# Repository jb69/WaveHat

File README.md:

# WaveHat: a sea-state sensor for Signal K, on a Seeed XIAO

A small carrier board ("hat") for a **Seeed XIAO ESP32-C3, C6 or S3** with an ST **LSM6DSO** motion sensor, an **SN65HVD230** CAN transceiver and **256 MB of soldered log storage**. On a yacht it measures how the boat moves and turns that into **heave, significant wave height and wave period** for [Signal K](https://signalk.org), and listens on the NMEA 2000 backbone. The same board runs an eFoil's telemetry node under [VESC Express](https://github.com/vedderb/vesc_express).

## Why

Signal K knows the depth, the wind, the current and even a forecast wave height. It has no **measured** sea state. `environment.heave` is in the specification, and almost nothing fills it; there is no path at all for a measured wave height or period. A boat at anchor is a perfectly good wave buoy if you do the maths on its motion.

## What is here

| Path | What | Licence |
|---|---|---|
| [`hardware/kicad-revB/`](hardware/kicad-revB/) | **Rev B**, the current board (21 × 69 mm): KiCad 10 project, Gerbers, BOM, pick-and-place, JLCPCB and Seeed order packs, and the Python generator that builds all of it from one description | CERN-OHL-S 2.0 |
| [`hardware/kicad/`](hardware/kicad/) | Rev A (21 × 54 mm), the first boards built | CERN-OHL-S 2.0 |
| [`hardware/DESIGN.md`](hardware/DESIGN.md) | Requirements, layout, pin use for C3 / C6 / S3, power, CAN, manufacturing, and what rev A taught (§11) | |
| [`hardware/test-plate/`](hardware/test-plate/) | A printed jig and checklist for testing every via on a bare rev A board | CERN-OHL-S 2.0 |
| [`enclosure/`](enclosure/) | Printable gasketed enclosure: parametric OpenSCAD and STLs | CERN-OHL-S 2.0 |
| [`firmware/`](firmware/) | SensESP firmware (heave, Hs, Tp, Tz to Signal K; NMEA 2000 in, listen-only; on-board CSV log; GNSS port; battery mode), the wave maths in C++ and Python with its test harness and accuracy results, and VESC Express board files | MIT |
| [`signalk-plugin/`](signalk-plugin/) | `signalk-seastate`: a Signal K server plugin that makes a sea state from the heave a Precision-9 compass already puts on NMEA 2000 (PGN 127252). No WaveHat needed | MIT |
| [`docs/signalk-sea-state.md`](docs/signalk-sea-state.md) | The write-up: the gap in Signal K, what the maths does, where the paths land in the spec, and how a boat with a heave-capable compass can try it with no hardware | |
| [`REVIEW.md`](REVIEW.md) | A critical review of the plan and the maths against the objective (21 Oct 2026) | |

## What it sends

| Signal K path | Units | Spec status |
|---|---|---|
| `environment.heave` | m, up positive, 4 Hz | **Standard** |
| `environment.waves.significantHeight` | m, every ~79 s over the last ~20 min | Proposed; mirrors the Weather API's `waveSignificantHeight` |
| `environment.waves.period` | s, peak period Tp; null with no clear peak | Proposed; mirrors `wavePeriod` |
| `environment.waves.meanPeriod` | s, zero-crossing period Tz | Proposed |
| `environment.waves.underway` | bool: the window was taken with the boat moving | Proposed |

How: a Mahony filter finds "up", the acceleration is moved to the hull's roll/pitch centre (you enter where the box is mounted) and rotated to vertical, high-passed at 0.02 Hz and integrated twice to heave; a Welch spectrum over 0.04–0.5 Hz gives Hs = 4 √m0, Tp and Tz. Details and accuracy on synthetic seas (Hs within about 3 % RMS after calibration) are in [`firmware/README.md`](firmware/README.md).

## Status (9 Nov 2026)

Honest version: **no yacht has been to sea with one yet.** The board itself has, in an eFoil.

- **Rev A:** five boards built by JLCPCB in October 2026; brought up on the bench and in service in eFoils under VESC Express. They had open vias from the fab's plating; rev B's layout changes (twinned vias, a test pad per layer crossing) come from that.
- **Rev B:** laid out, checked (ERC 0, DRC 0 errors) and ordered on 7 Nov 2026. Adds a GNSS port (J5), a 10-pin IO header (J6), jumpers that isolate the CAN transceiver (JP8–JP10) and a 1S battery option (J7). Not yet received.
- **Firmware:** builds for all three XIAOs; the wave maths is tested on the desktop and on a bare XIAO C3. The rev B features (GNSS, battery mode with wake-on-motion, bus heave logging) are written and build, and have not run on a board.
- **Signal K plugin:** maths tested against known seas; not yet run against a real compass.

## Limits

- It measures the **boat's** motion, not the water's. A hull filters short chop and can exaggerate swell near its own roll period: expect ±20–30 % on wave height at anchor until it is compared with a buoy.
- **Underway**, waves are met faster or slower than their true period, so periods mean something only at anchor or drifting. The `underway` flag says which.
- One sensor gives no reliable wave **direction**.
- A DIY NMEA 2000 node isn't certified. This one only listens: it never transmits, not even an acknowledge.

## Building one

- **Board:** the order packs in [`hardware/kicad-revB/fab/`](hardware/kicad-revB/fab/) go straight to JLCPCB (`ORDER.md` in each pack has the form settings). Choose electroless copper plating for the vias explicitly.
- **Regenerating the layout:** `hardware/kicad-revB/run_pipeline.sh` needs KiCad 10, Java and [Freerouting](https://github.com/freerouting/freerouting) 2.4.1; point the `FREEROUTING` environment variable at the jar.
- **Firmware:** [PlatformIO](https://platformio.org) with Python 3.10 or newer, then `pio run -e xiao_c3 -t upload` in `firmware/`.
- **Enclosure:** print the base and lid in ASA or PETG and the gasket in TPU; [`enclosure/README.md`](enclosure/README.md).

## Origin

The circuit comes from the telemetry node of a restored Takuma Cruiser V1 eFoil: a XIAO ESP32-C3 with an LSM6DSO and an SN65HVD230 on the ESC's CAN bus, running VESC Express in a sealed box (write-up: foil.zone thread 27157, "Bringing a Dead Takuma Cruiser V1 Back to Life"). WaveHat puts that on one factory-assembled board, keeps its pinout, and adds marine power input, NMEA 2000 and rigid mounting. Some documents here refer to that project's private notes by path; those notes are not in this repository.

## Licences

- Hardware (`hardware/`, `enclosure/`): [CERN-OHL-S 2.0](hardware/LICENSE).
- Software (`firmware/`, `signalk-plugin/`, the generator scripts): [MIT](LICENSE).
- The XIAO footprint in `hardware/kicad*/lib/seeed/` is from Seeed's OPL KiCad library, CC BY-SA 4.0.

## Sources

- ST LSM6DSO: datasheet DS12140, application note AN5192.
- Seeed XIAO pin maps: [ESP32-C3](https://wiki.seeedstudio.com/XIAO_ESP32C3_Getting_Started/), [ESP32-C6](https://wiki.seeedstudio.com/xiao_esp32c6_getting_started/), [ESP32-S3](https://wiki.seeedstudio.com/xiao_esp32s3_getting_started/).
- [VESC Express](https://github.com/vedderb/vesc_express), hardware target `hw_seeed_esp32c3`.
- [Signal K specification](https://github.com/SignalK/specification) and the server's Weather API.
- TI LMR51606 datasheet SLUSEY1B.

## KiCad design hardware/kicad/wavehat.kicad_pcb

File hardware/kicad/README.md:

# WaveHat KiCad project

KiCad 10 schematic and PCB for WaveHat rev A, plus everything needed to order it.

## Files
| File | What |
|---|---|
| `wavehat.kicad_pro`, `wavehat.kicad_sch`, `wavehat.kicad_pcb` | The project. Open `wavehat.kicad_pro` in KiCad |
| `wavehat-schematic.pdf` | Schematic as PDF |
| **`fab/seeed/`** | **Ready for Seeed Fusion**: Gerbers named as Seeed asks, Seeed-format BOMs (with a XIAO C3 / C6 / S3 from Seeed's Open Parts Library, or without), two-sided pick-and-place, assembly drawings, one zip per option, and `ORDER.md` (copied from `ORDER-SEEED.md`) with what to pick on the order forms |
| **`fab/jlcpcb/no-storage/`, `fab/jlcpcb/full/`** | JLCPCB assembly quotes for the top-side-only build and the full two-sided build: JLCPCB-format BOM with LCSC part numbers, CPL (no XIAO), the same Gerbers, and `ORDER.md` (from `ORDER-JLCPCB.md` / `ORDER-JLCPCB-FULL.md`) |
| `fab/wavehat-gerbers.zip` | Gerbers + drill (KiCad names), for PCBWay / JLCPCB |
| `fab/wavehat-bom.csv`, `fab/wavehat-cpl-top.csv`, `fab/wavehat-cpl-bottom.csv` | BOM and pick-and-place for each side (DNP excluded), mm from the board's lower-left corner |
| `img/` | 3D renders, top, bottom and angled |
| `reports/erc.json`, `reports/drc.json` | The last ERC and DRC runs |
| `reports/vias.md` | Every via by net and position, for checking boards with open vias (rev A had some) |
| `lib/wavehat.kicad_sym`, `lib/wavehat.pretty/` | Custom symbols (XIAO 14-pad, LSM6DSO, LMR51606, SD NAND) and footprints (XIAO 14-pad, NMEA 2000 pads, SD NAND LGA-8 8 × 6 mm) |
| `lib/seeed/` | Seeed's original XIAO library files the XIAO footprint is derived from (CC BY-SA 4.0) |
| `wavehat_design.py` | **The source.** Every part, footprint, connection, schematic position and board position |
| `gen_schematic.py`, `gen_pcb.py`, `gen_docs.py`, `gen_seeed.py`, `run_pipeline.sh` | Generators and the end-to-end script |
| `ORDER-SEEED.md` | Seeed Fusion order notes (source of `fab/seeed/ORDER.md`) |

## How it's built
Everything comes from `wavehat_design.py`:
1. `gen_schematic.py` writes the schematic. Every pin gets a short wire and a net label, so the drawing is a connectivity schematic rather than a hand-drawn one. It is checked with `kicad-cli sch erc`.
2. `gen_pcb.py place` builds the board in KiCad's own Python: outline, footprints linked to the schematic symbols by UUID (top, or bottom for the log storage), nets, keep-outs (nothing under the IMU; no vias near the XIAO's underside pads or the fiducials), silkscreen, the drill/place origin at the lower-left corner, and the design rules in the project file. It exports a Specctra DSN with the clearance raised to 0.17 mm for the router.
3. **Freerouting** routes every net, ground included.
4. `gen_pcb.py import` brings the routes back, widens the few pad-entry segments Freerouting thins below 0.15 mm (the 0.02 mm routing margin keeps their clearance), adds ground stitching vias where they clear everything, pours ground on both layers, fills, and removes any stitching via the pour left in an island.
5. `kicad-cli pcb drc --schematic-parity` checks it. If DRC finds an error or anything unconnected, steps 2–5 repeat from a freshly placed board with a different number of Freerouting passes (100, 150, 200, 80, 250, 120), up to six times. The script then exports Gerbers, drill, BOM, both CPLs, the PDF and renders; `gen_docs.py` regenerates `../netlist.md` and `../bom.csv`, and `gen_seeed.py` builds `fab/seeed/`.

To change the design, edit `wavehat_design.py` and run:

```bash
FREEROUTING=/path/to/freerouting-2.4.1.jar ./run_pipeline.sh
```

Hand edits in KiCad are fine too, but they are overwritten the next time the pipeline runs. Once you start polishing the layout by hand, stop regenerating the PCB, and keep `wavehat_design.py` for the schematic and docs only.

## Rules
| | |
|---|---|
| Signal track / clearance | 0.15 mm / 0.15 mm (6 mil, base capability at PCBWay, JLCPCB, Seeed Fusion) |
| Power track (VIN_RAW, VIN_FUSED, VIN, SW, 5V_BUCK, 5V_CAN, XIAO_5V) | 0.4 mm |
| Vias | 0.6 mm pad / 0.3 mm drill, tented |
| Copper to edge | 0.3 mm |

## Last check (20 Oct 2026: log storage, 5–30 V input)
ERC 0 violations · DRC 0 errors, 0 unconnected · schematic parity 0 issues · 59 silkscreen warnings (cosmetic).

## Tools used
- KiCad 10.0.7 (Homebrew cask `kicad`), using `kicad-cli` and the bundled Python `pcbnew` module.
- Freerouting 2.4.1 (https://github.com/freerouting/freerouting/releases/tag/v2.4.1), SHA-256 `251101c3eeac22d7e7dfcf6796603279e5d1000283eb82d8f093780f7afc6aa9`, checked against GitHub's published asset digest. The newest release (2.5.0) was skipped as less than two weeks old.
- OpenJDK (Homebrew `openjdk`) to run Freerouting.

## Sources and licences
- XIAO footprint: derived from Seeed-Studio/OPL_Kicad_Library `XIAO-ESP32-C3-SMD` (pads 15 and up removed so it fits the C3, C6 and S3). That library is **CC BY-SA 4.0**, so `lib/wavehat.pretty/XIAO_ESP32_14P_SMD.kicad_mod` is too. Pad map checked against Seeed's C3, C6 and S3 SMD footprints and symbols.
- LSM6DSO pin functions: ST application note AN5192. LMR51606 pins and the 5 V component values: TI datasheet SLUSEY1B.
- SD NAND pinout (SPI mode) and LGA-8 package: Zetta ZDSD01G/02G/04G datasheet (LCSC C2875853), MK MKDV4GCL (C7500178), CS-Creative CSNP4GCR01 and XTX XTSD04G datasheets; all share the pinout and 8 × 6 mm package.
- Other symbols and footprints: the KiCad standard libraries (CC BY-SA 4.0 with KiCad's exception for designs that use them).
- Circuit origin: the Takuma project's XIAO node (see `../DESIGN.md` §0).

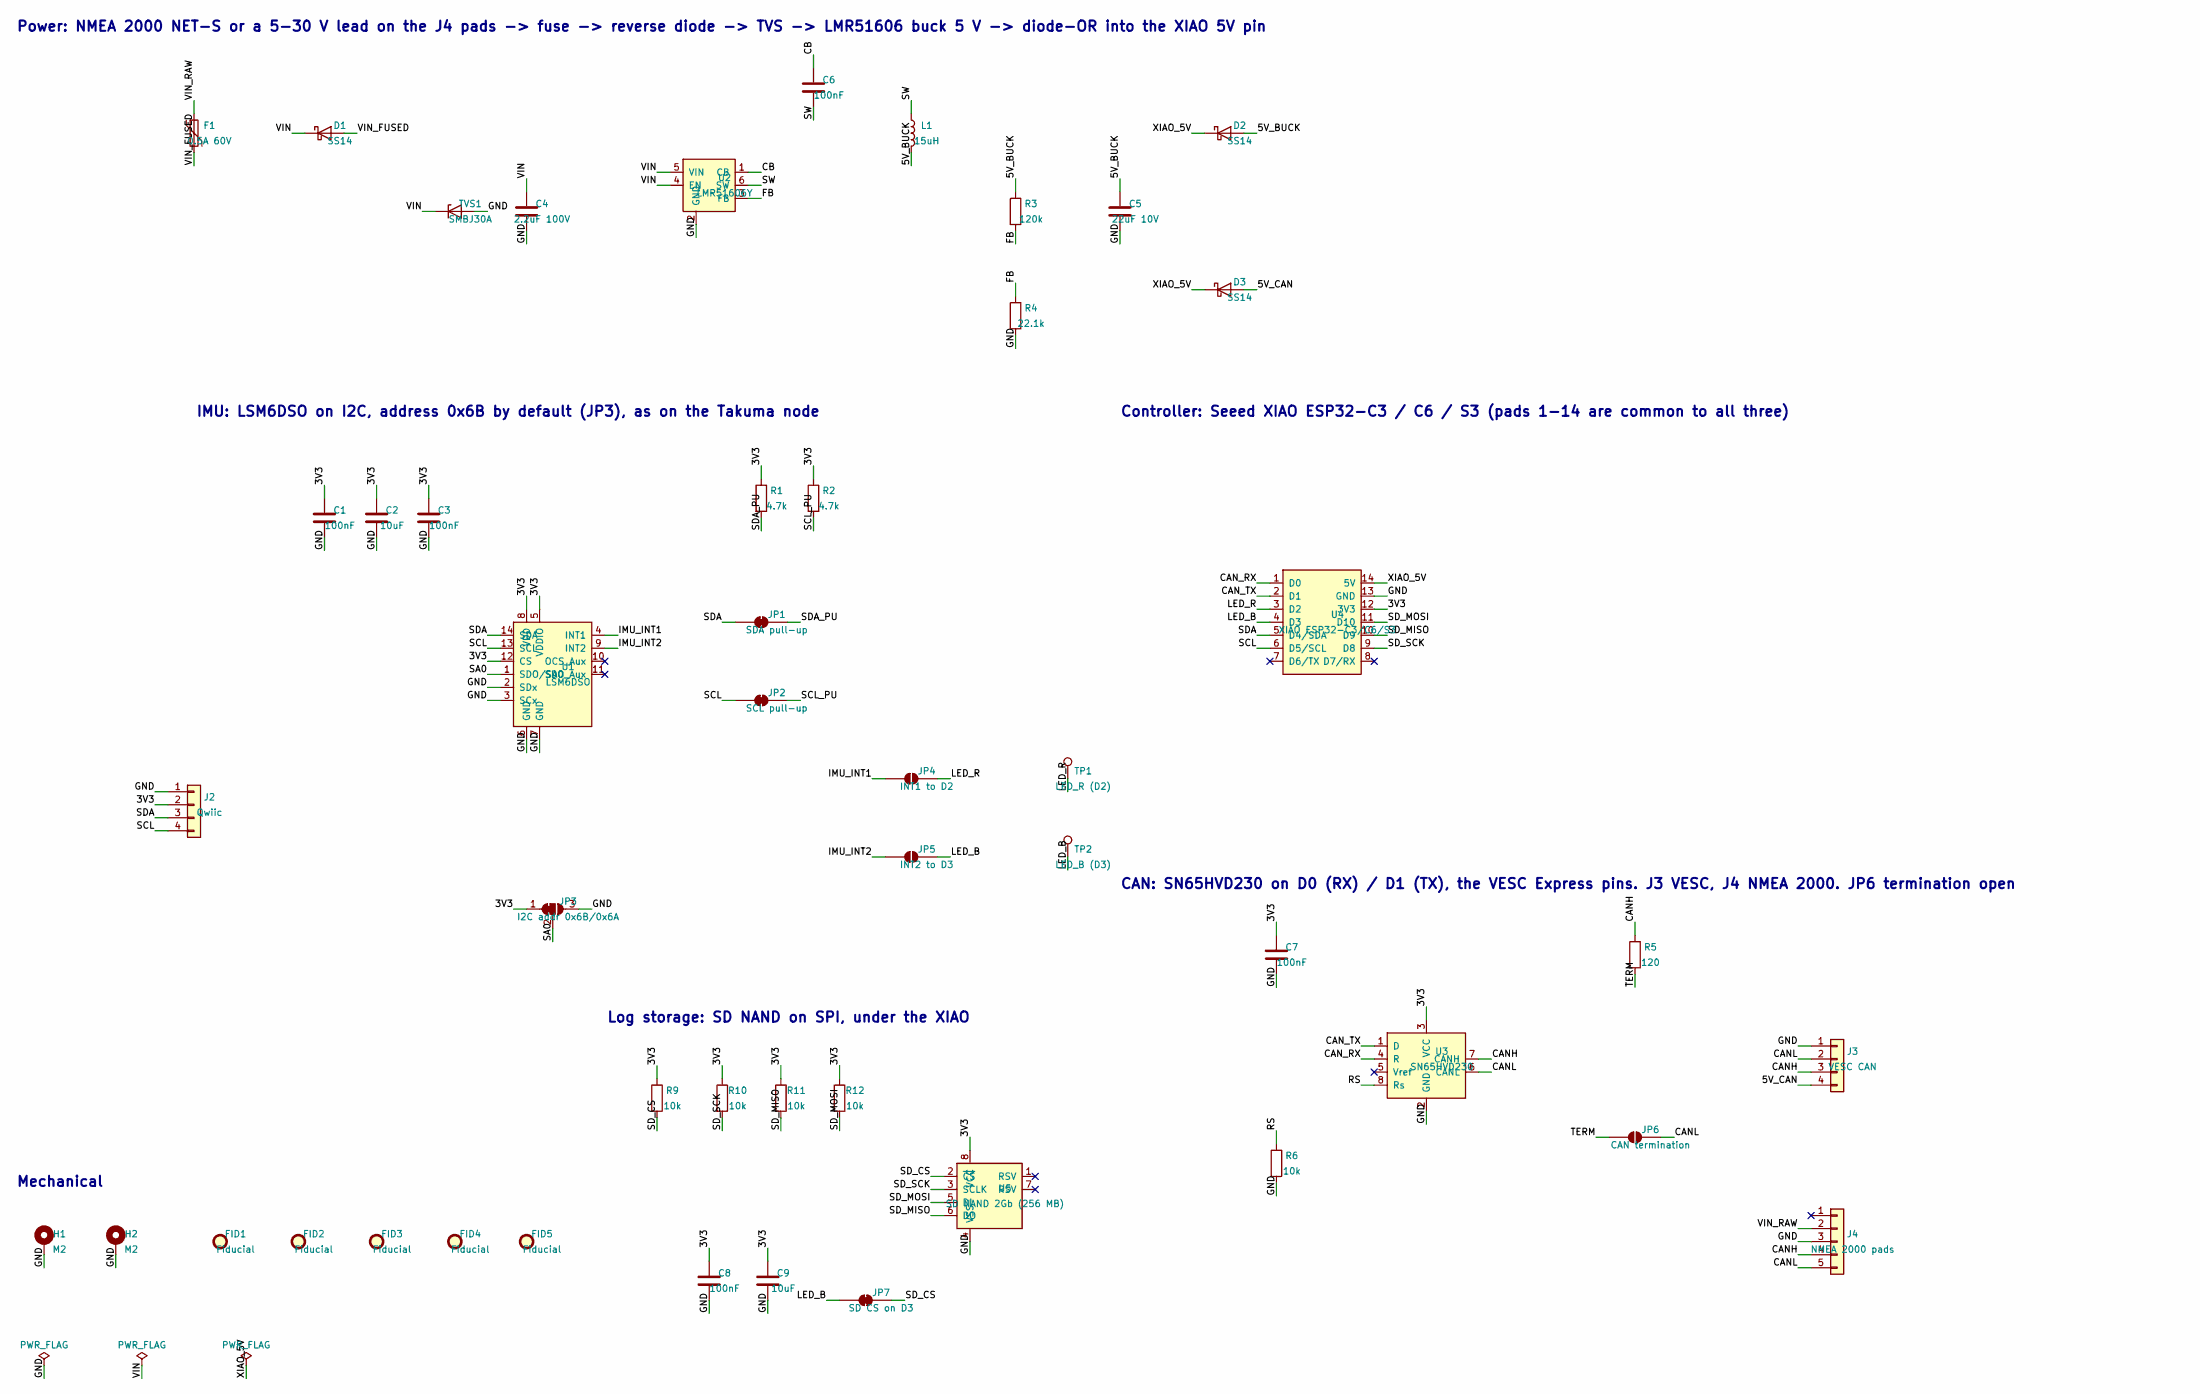
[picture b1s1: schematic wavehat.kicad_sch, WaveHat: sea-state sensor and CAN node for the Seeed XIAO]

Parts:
C1, C3, C6, C7, C8: 100nF; C_0402_1005Metric; MPN GRM155R71C104KA88D
C2, C9: 10uF; C_0603_1608Metric; MPN GRM188R61A106KE69D
C4: 2.2uF 100V; C_1206_3216Metric; MPN GRM31CR72A225KA73L
C5: 22uF 10V; C_0805_2012Metric; MPN GRM21BR61A226ME51L
D1, D2, D3: SS14; D_SMA; MPN SS14
F1: 0.5A 60V; Fuse_1812_4532Metric; MPN 1812L050/60MR
FID1, FID2, FID3, FID4, FID5: Fiducial; Fiducial_1mm_Mask2mm
H1, H2: M2; MountingHole_2.2mm_M2_Pad
J2: Qwiic; JST_SH_SM04B-SRSS-TB_1x04-1MP_P1.00mm_Horizontal; MPN SM04B-SRSS-TB(LF)(SN)
J3: VESC CAN; JST_GH_SM04B-GHS-TB_1x04-1MP_P1.25mm_Horizontal; MPN SM04B-GHS-TB(LF)(SN)
J4: NMEA 2000 pads; N2K_Pads_1x05_P3.0mm
JP1: SDA pull-up; SolderJumper-2_P1.3mm_Bridged_RoundedPad1.0x1.5mm
JP2: SCL pull-up; SolderJumper-2_P1.3mm_Bridged_RoundedPad1.0x1.5mm
JP3: I2C addr 0x6B/0x6A; SolderJumper-3_P1.3mm_Bridged12_RoundedPad1.0x1.5mm
JP4: INT1 to D2; SolderJumper-2_P1.3mm_Open_RoundedPad1.0x1.5mm
JP5: INT2 to D3; SolderJumper-2_P1.3mm_Open_RoundedPad1.0x1.5mm
JP6: CAN termination; SolderJumper-2_P1.3mm_Open_RoundedPad1.0x1.5mm
JP7: SD CS on D3; SolderJumper-2_P1.3mm_Bridged_RoundedPad1.0x1.5mm
L1: 15uH; L_Changjiang_FNR4020S; MPN FNR4020S150MT
R1, R2: 4.7k; R_0402_1005Metric; MPN RC0402FR-074K7L
R3: 120k; R_0402_1005Metric; MPN RC0402FR-07120KL
R4: 22.1k; R_0402_1005Metric; MPN RC0402FR-0722K1L
R5: 120; R_0402_1005Metric; MPN RC0402FR-07120RL
R6, R9, R10, R11, R12: 10k; R_0402_1005Metric; MPN RC0402FR-0710KL
TP1: LED_R (D2); TestPoint_Pad_D1.5mm
TP2: LED_B (D3); TestPoint_Pad_D1.5mm
TVS1: SMBJ30A; D_SMB; MPN SMBJ30A
U1: LSM6DSO; LGA-14_3x2.5mm_P0.5mm_LayoutBorder3x4y; MPN LSM6DSOTR
U2: LMR51606Y; SOT-23-6; MPN LMR51606YDBVR
U3: SN65HVD230; SOIC-8_3.9x4.9mm_P1.27mm; MPN SN65HVD230DR
U4: XIAO ESP32-C3/C6/S3; XIAO_ESP32_14P_SMD; MPN Seeed XIAO ESP32C3 113991054 (or C6 113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
U5: SD NAND 2Gb (256 MB); SD_NAND_LGA-8_8x6mm_P1.27mm; MPN ZDSD02GLGEAG

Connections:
/3V3: C1.1, C2.1, C3.1, C7.1, C8.1, C9.1, J2.2, JP3.1 (A), R1.1, R2.1, R9.1, R10.1, R11.1, R12.1, U1.5 (VDDIO), U1.8 (VDD), U1.12 (CS), U3.3 (VCC), U4.12 (3V3), U5.8 (VCC)
/5V_BUCK: C5.1, D2.2 (A), L1.2, R3.1
/5V_CAN: D3.2 (A), J3.4
/CANH: J3.3, J4.4, R5.1, U3.7 (CANH)
/CANL: J3.2, J4.5, JP6.2 (B), U3.6 (CANL)
/CAN_RX: U3.4 (R), U4.1 (D0)
/CAN_TX: U3.1 (D), U4.2 (D1)
/CB: C6.1, U2.1 (CB)
/FB: R3.2, R4.1, U2.3 (FB)
/GND: C1.2, C2.2, C3.2, C4.2, C5.2, C7.2, C8.2, C9.2, H1.1, H2.1, J2.1, J3.1, J4.3, JP3.3 (B), R4.2, R6.2, TVS1.2 (A), U1.2 (SDx), U1.3 (SCx), U1.6 (GND), U1.7 (GND), U2.2 (GND), U3.2 (GND), U4.13 (GND), U5.4 (VSS)
/IMU_INT1: JP4.1 (A), U1.4 (INT1)
/IMU_INT2: JP5.1 (A), U1.9 (INT2)
/LED_B: JP5.2 (B), JP7.1 (A), TP2.1, U4.4 (D3)
/LED_R: JP4.2 (B), TP1.1, U4.3 (D2)
/RS: R6.1, U3.8 (Rs)
/SA0: JP3.2 (C), U1.1 (SDO/SA0)
/SCL: J2.4, JP2.1 (A), U1.13 (SCL), U4.6 (D5/SCL)
/SCL_PU: JP2.2 (B), R2.2
/SDA: J2.3, JP1.1 (A), U1.14 (SDA), U4.5 (D4/SDA)
/SDA_PU: JP1.2 (B), R1.2
/SD_CS: JP7.2 (B), R9.2, U5.2 (~CS)
/SD_MISO: R11.2, U4.10 (D9), U5.6 (DO)
/SD_MOSI: R12.2, U4.11 (D10), U5.5 (DI)
/SD_SCK: R10.2, U4.9 (D8), U5.3 (SCLK)
/SW: C6.2, L1.1, U2.6 (SW)
/TERM: JP6.1 (A), R5.2
/VIN: C4.1, D1.1 (K), TVS1.1 (K), U2.4 (EN), U2.5 (VIN)
/VIN_FUSED: D1.2 (A), F1.2
/VIN_RAW: F1.1, J4.2
/XIAO_5V: D2.1 (K), D3.1 (K), U4.14 (5V)

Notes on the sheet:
Power: NMEA 2000 NET-S or a 5-30 V lead on the J4 pads -> fuse -> reverse diode -> TVS -> LMR51606 buck 5 V -> diode-OR into the XIAO 5V pin
IMU: LSM6DSO on I2C, address 0x6B by default (JP3), as on the Takuma node
Controller: Seeed XIAO ESP32-C3 / C6 / S3 (pads 1-14 are common to all three)
CAN: SN65HVD230 on D0 (RX) / D1 (TX), the VESC Express pins. J3 VESC, J4 NMEA 2000. JP6 termination open
Log storage: SD NAND on SPI, under the XIAO
Mechanical

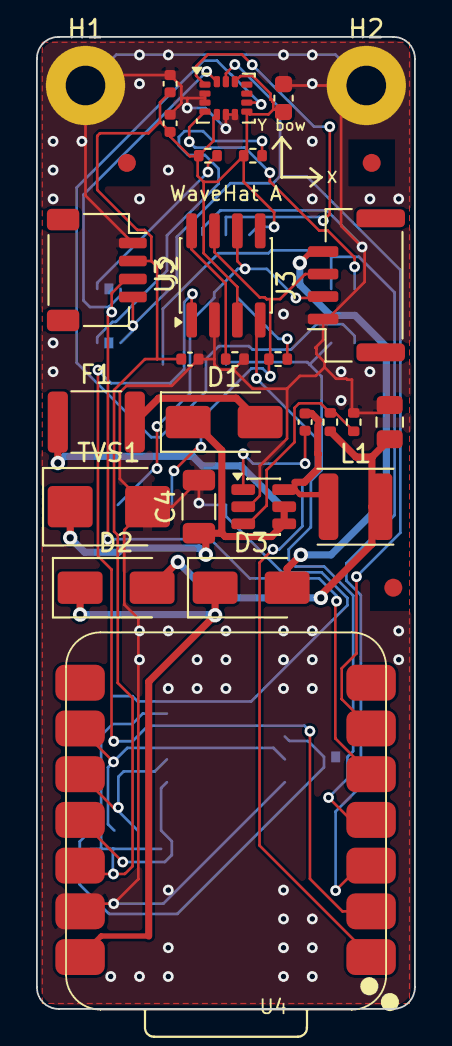
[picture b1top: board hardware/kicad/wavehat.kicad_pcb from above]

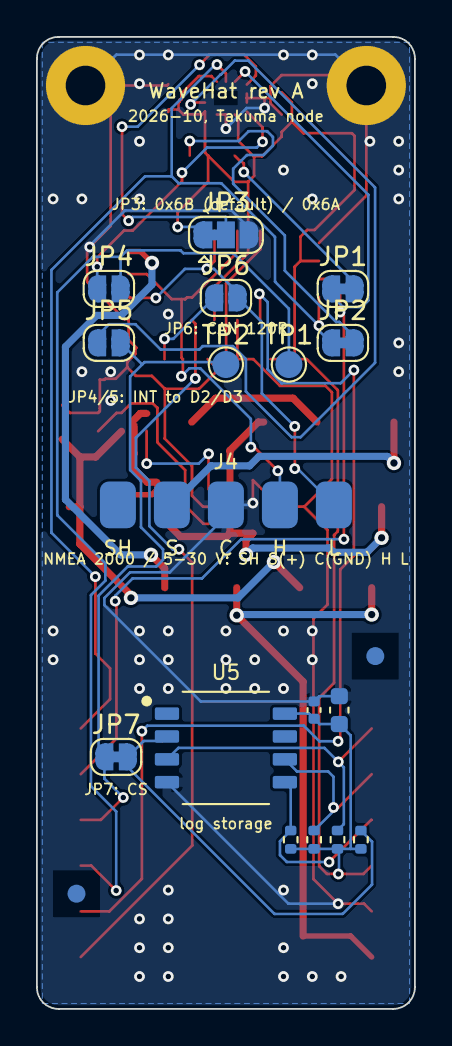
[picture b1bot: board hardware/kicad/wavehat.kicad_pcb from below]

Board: 2 copper layers, 21.0 x 54.0 mm, 49 parts (19 on the bottom side), 30 nets.

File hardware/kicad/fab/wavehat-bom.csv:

"Designator","Value","Footprint","MPN","Qty","DNP"
"C1,C3,C6,C7,C8","100nF","Capacitor_SMD:C_0402_1005Metric","GRM155R71C104KA88D","5",""
"C2,C9","10uF","Capacitor_SMD:C_0603_1608Metric","GRM188R61A106KE69D","2",""
"C4","2.2uF 100V","Capacitor_SMD:C_1206_3216Metric","GRM31CR72A225KA73L","1",""
"C5","22uF 10V","Capacitor_SMD:C_0805_2012Metric","GRM21BR61A226ME51L","1",""
"D1,D2,D3","SS14","Diode_SMD:D_SMA","SS14","3",""
"F1","0.5A 60V","Fuse:Fuse_1812_4532Metric","1812L050/60MR","1",""
"J2","Qwiic","Connector_JST:JST_SH_SM04B-SRSS-TB_1x04-1MP_P1.00mm_Horizontal","SM04B-SRSS-TB(LF)(SN)","1",""
"J3","VESC CAN","Connector_JST:JST_GH_SM04B-GHS-TB_1x04-1MP_P1.25mm_Horizontal","SM04B-GHS-TB(LF)(SN)","1",""
"L1","15uH","Inductor_SMD:L_Changjiang_FNR4020S","FNR4020S150MT","1",""
"R1,R2","4.7k","Resistor_SMD:R_0402_1005Metric","RC0402FR-074K7L","2",""
"R3","120k","Resistor_SMD:R_0402_1005Metric","RC0402FR-07120KL","1",""
"R4","22.1k","Resistor_SMD:R_0402_1005Metric","RC0402FR-0722K1L","1",""
"R5","120","Resistor_SMD:R_0402_1005Metric","RC0402FR-07120RL","1",""
"R6,R9,R10,R11,R12","10k","Resistor_SMD:R_0402_1005Metric","RC0402FR-0710KL","5",""
"TVS1","SMBJ30A","Diode_SMD:D_SMB","SMBJ30A","1",""
"U1","LSM6DSO","Package_LGA:LGA-14_3x2.5mm_P0.5mm_LayoutBorder3x4y","LSM6DSOTR","1",""
"U2","LMR51606Y","Package_TO_SOT_SMD:SOT-23-6","LMR51606YDBVR","1",""
"U3","SN65HVD230","Package_SO:SOIC-8_3.9x4.9mm_P1.27mm","SN65HVD230DR","1",""
"U4","XIAO ESP32-C3/C6/S3","wavehat:XIAO_ESP32_14P_SMD","Seeed XIAO ESP32C3 113991054 (or C6 113991254 / S3 113991114)","1",""
"U5","SD NAND 2Gb (256 MB)","wavehat:SD_NAND_LGA-8_8x6mm_P1.27mm","ZDSD02GLGEAG","1",""

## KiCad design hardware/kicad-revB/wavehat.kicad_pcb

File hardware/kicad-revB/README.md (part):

# WaveHat rev B KiCad project

KiCad 10 schematic and PCB for WaveHat **rev B**, started 30 Oct 2026 from the rev A project (`../kicad/`, which stays as ordered for the quality case and the test jig). Same generator pipeline; the rev B changes are in `wavehat_design.py` and the generators, listed below. Routed and DRC-clean on 30 Oct 2026; fab outputs in `fab/`. Not yet ordered, and not yet checked by eye in KiCad (DESIGN.md §13 still applies).

## What changed from rev A
| Change | Where |
|---|---|
| Board 21 × **69** mm: 8 mm added behind the sensor zone (holes, IMU, decoupling, pull-ups stay where they were; everything aft moved 8 mm), then 7 mm more at the J2/J6 band on 7 Nov 2026 for the IO header (everything from the fuse aft moved again) | `wavehat_design.py` `BOARD_L`, `SHIFT`, `SHIFT2` |
| **J6 IO header** (7 Nov 2026): 10-pin JST-GH on the left-hand edge forward of J2, 1 5V, 2 3V3, 3 GND, 4 D2, 5 D3, 6 D6, 7 D7, 8 D0, 9 D1, 10 GND, so leads for LEDs, a remote's UART, ESC telemetry or a mast sensor plug in instead of being soldered to the XIAO. Fitted (LCSC C2683602). J2 moved aft to y 30.2 | `wavehat_design.py` J6, J2 |
| **JP8, JP9, JP10** (7 Nov 2026): bridged solder jumpers in U3's 3V3, RXD and TXD. Cut all three (and open JP6) for a build with no CAN: U3 is then unpowered and off D0/D1, which are free on J6 | `wavehat_design.py` U3, C7, JP8–JP10 |
| **Battery option** (7 Nov 2026): XIAO footprint pads 15/16 (under the C3/S3 VBAT/GND pads) and 17/18 (under the C6's), paste on, so the module's own 1S charger is reachable; VBAT (0.4 mm) to **J7**, two 2.54 mm holes by J6 for a cell pigtail (DNP, pin 1 +) | `gen_schematic.py` `xiao_footprint()`, `wavehat_design.py` U4, J7 |
| **J5 GNSS port**: 6-pin JST-GH, Pixhawk GPS pinout (5V, TX, RX, SCL, SDA, GND), UART on XIAO D6/D7. On the right-hand edge aft of J3, opening flush with the edge like J2 and J3, so the plug slides in from outside the board (a connector facing along the board would have the IMU and C2 in the plug's path). J3 moved forward to sit beside the transceiver. DNP | `wavehat_design.py` J5, J3 |
| Buck parts that J5 displaced: C5 beside L1, R3/R4/C6 in a row between J5 and the inductor, L1 0.9 mm aft; FID3 to the free band behind the sensor zone (the XIAO covers the stern) | `wavehat_design.py` |
| **30 test pads** TP1–TP30 on the bottom, 1.0 mm, 2.54 mm grid, one per layer-crossing net plus GND, numbered on the silk; `reports/test-pads.md` lists them with their component-side partner | `wavehat_design.py` `TEST_PADS`, `gen_docs.py` |
| **Twin vias**: after routing, every non-GND via gets a second one 0.8–2.0 mm away, linked on both layers by a straight or L-shaped stub, wherever that clears the design rules. On the 7 Nov 2026 routing 43 of 102 signal and power vias got a twin; the other 59 are in spots too tight (the IMU fanout against the bow edge, under U3, the SD NAND lands, the J6 fanout) and stay single. `reports/vias.md` lists every via, twinned or not | `gen_pcb.py` `twin_vias()`, `via_report()` |
| **Pour cut** is added after routing, not before: the Specctra export turns any rule area into a full track keepout, which walled the IMU off on the first run | `gen_pcb.py` `pour_cut()` |
| **XIAO lands 3.45 × 2.0 mm**, grown outboard so 1.4 mm shows past the module; paste stays on the rev A 2.75 mm | `gen_schematic.py` `xiao_pad_rev_b()` |
| **3V3 in a 0.3 mm "Supply" net class** (rev A: 0.15 mm) | `gen_pcb.py` `RULES`, `D.SUPPLY_NETS` |
| **Pour cut** across the board at y 8.6: no copper fill crosses between the sensor zone and the rest | `gen_pcb.py` rule area "sensor zone: pour cut" |
| Silkscreen tidied: jumper labels no longer overlap, big parts' references on Fab | `gen_pcb.py` |
| Fab note: via plating **Horizontal Electroless Copper** | title block, `ORDER-JLCPCB-FULL.md` |

Not done (needs a wider board): mounting holes at the stern end. The XIAO spans the width to within 1.75 mm of each edge, so a second pair of M2 holes needs a 27 mm board; rev B keeps 21 mm and the enclosure's stern rail. The enclosure (`../../enclosure/`) needs `pcb_l` set to 69 for rev B.

## Files
| File | What |
|---|---|
| `wavehat.kicad_pro`, `wavehat.kicad_sch`, `wavehat.kicad_pcb` | The project. Open `wavehat.kicad_pro` in KiCad |
| `wavehat-schematic.pdf` | Schematic as PDF |
| **`fab/seeed/`** | **Ready for Seeed Fusion**: Gerbers named as Seeed asks, Seeed-format BOMs (with a XIAO C3 / C6 / S3 from Seeed's Open Parts Library, or without), two-sided pick-and-place, assembly drawings, one zip per option, and `ORDER.md` (copied from `ORDER-SEEED.md`) with what to pick on the order forms |
| **`fab/jlcpcb/no-storage/`, `fab/jlcpcb/full/`, `fab/jlcpcb/full-gnss/`** | JLCPCB assembly packs: top side only; the full two-sided build with J5 left off (hand-fit the GNSS port where wanted); and the full build **with J5 fitted** (LCSC C133065, Extended part). Each has the JLCPCB-format BOM with LCSC numbers, CPL (no XIAO), the same Gerbers and `ORDER.md` |
| `fab/wavehat-gerbers.zip` | Gerbers + drill (KiCad names), for PCBWay / JLCPCB |
| `fab/wavehat-bom.csv`, `fab/wavehat-cpl-top.csv`, `fab/wavehat-cpl-bottom.csv` | BOM and pick-and-place for each side (DNP excluded), mm from the board's lower-left corner. `fab/wavehat-cpl-top-with-dnp.csv` keeps J5, for the with-GNSS pack |
| `img/` | 3D renders, top, bottom and angled |
| `reports/erc.json`, `reports/drc.json` | The last ERC and DRC runs |
| `reports/test-pads.md` | The 30 bottom-side test pads: net, position, component-side partner (generated) |
| `reports/erc.json`, `reports/drc.json` | The last ERC and DRC runs |
| `reports/vias.md` | Every signal and power via with its twin, or the note that none fitted (generated) |
| `lib/wavehat.kicad_sym`, `lib/wavehat.pretty/` | Custom symbols (XIAO 14-pad, LSM6DSO, LMR51606, SD NAND) and footprints (XIAO 14-pad, NMEA 2000 pads, SD NAND LGA-8 8 × 6 mm) |
| `lib/seeed/` | Seeed's original XIAO library files the XIAO footprint is derived from (CC BY-SA 4.0) |
| `wavehat_design.py` | **The source.** Every part, footprint, connection, schematic position and board position |
| `gen_schematic.py`, `gen_pcb.py`, `gen_docs.py`, `gen_seeed.py`, `run_pipeline.sh` | Generators and the end-to-end script |
| `ORDER-SEEED.md` | Seeed Fusion order notes (source of `fab/seeed/ORDER.md`) |

## How it's built
Everything comes from `wavehat_design.py`:
1. `gen_schematic.py` writes the schematic. Every pin gets a short wire and a net label, so the drawing is a connectivity schematic rather than a hand-drawn one. It is checked with `kicad-cli sch erc`.
2. `gen_pcb.py place` builds the board in KiCad's own Python: outline, footprints linked to the schematic symbols by UUID (top, or bottom for the log storage), nets, keep-outs (nothing under the IMU; no vias near the XIAO's underside pads or the fiducials), silkscreen, the drill/place origin at the lower-left corner, and the design rules in the project file. It exports a Specctra DSN with the clearance raised to 0.17 mm for the router.
3. **Freerouting** routes every net, ground included.
4. `gen_pcb.py import` brings the routes back, widens the few pad-entry segments Freerouting thins below 0.15 mm (the 0.02 mm routing margin keeps their clearance), adds ground stitching vias where they clear everything, pours ground on both layers, fills, and removes any stitching via the pour left in an island.
5. `kicad-cli pcb drc --schematic-parity` checks it. If DRC finds an error or anything unconnected, steps 2–5 repeat from a freshly placed board with a different number of Freerouting passes (100, 150, 200, 80, 250, 120), up to six times. The script then exports Gerbers, drill, BOM, both CPLs, the PDF and renders; `gen_docs.py` regenerates `../netlist-revB.md`, `../bom-revB.csv` and `reports/test-pads.md`, and `gen_seeed.py` builds `fab/seeed/`.

To change the design, edit `wavehat_design.py` and run:

```bash
FREEROUTING=/path/to/freerouting-2.4.1.jar ./run_pipeline.sh
```

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
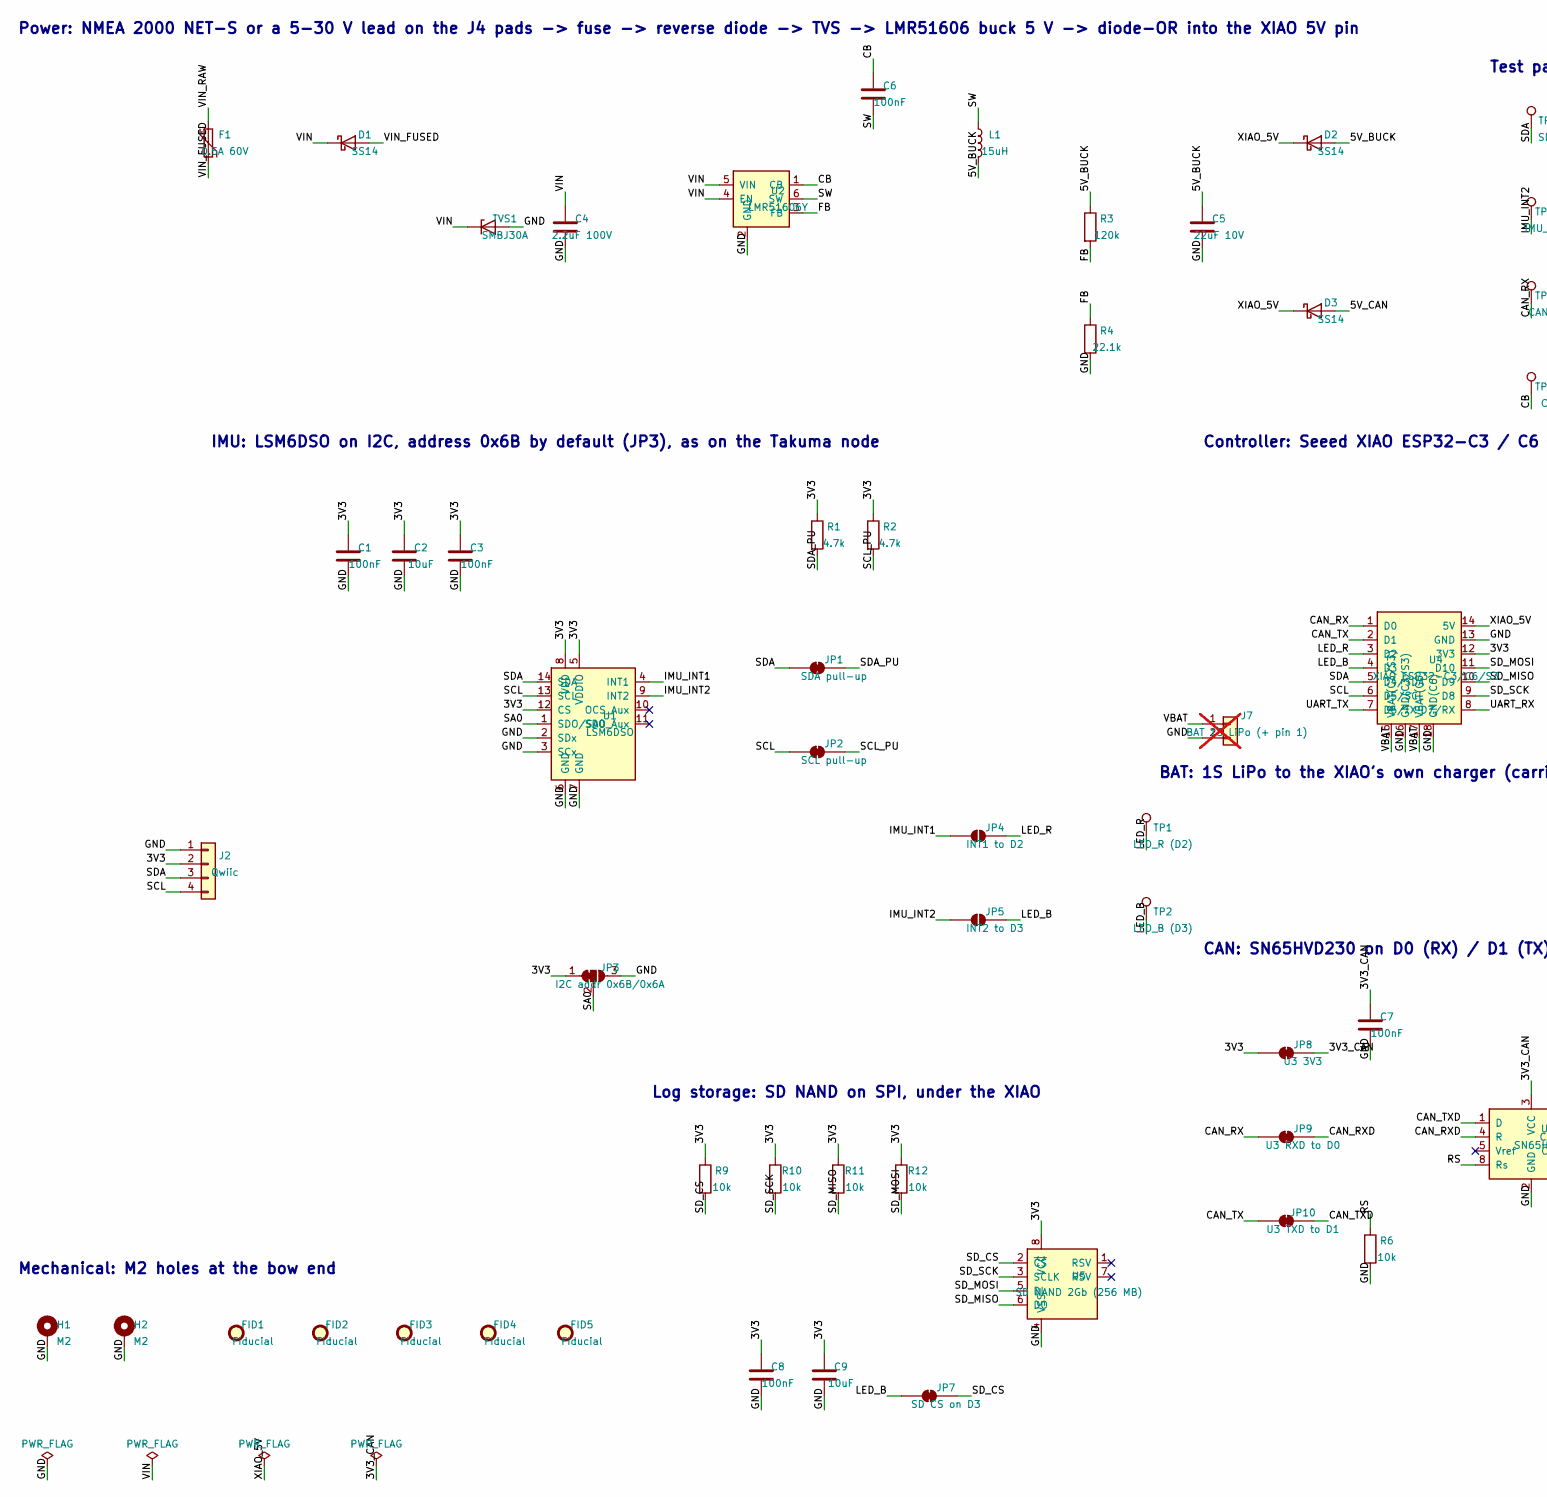
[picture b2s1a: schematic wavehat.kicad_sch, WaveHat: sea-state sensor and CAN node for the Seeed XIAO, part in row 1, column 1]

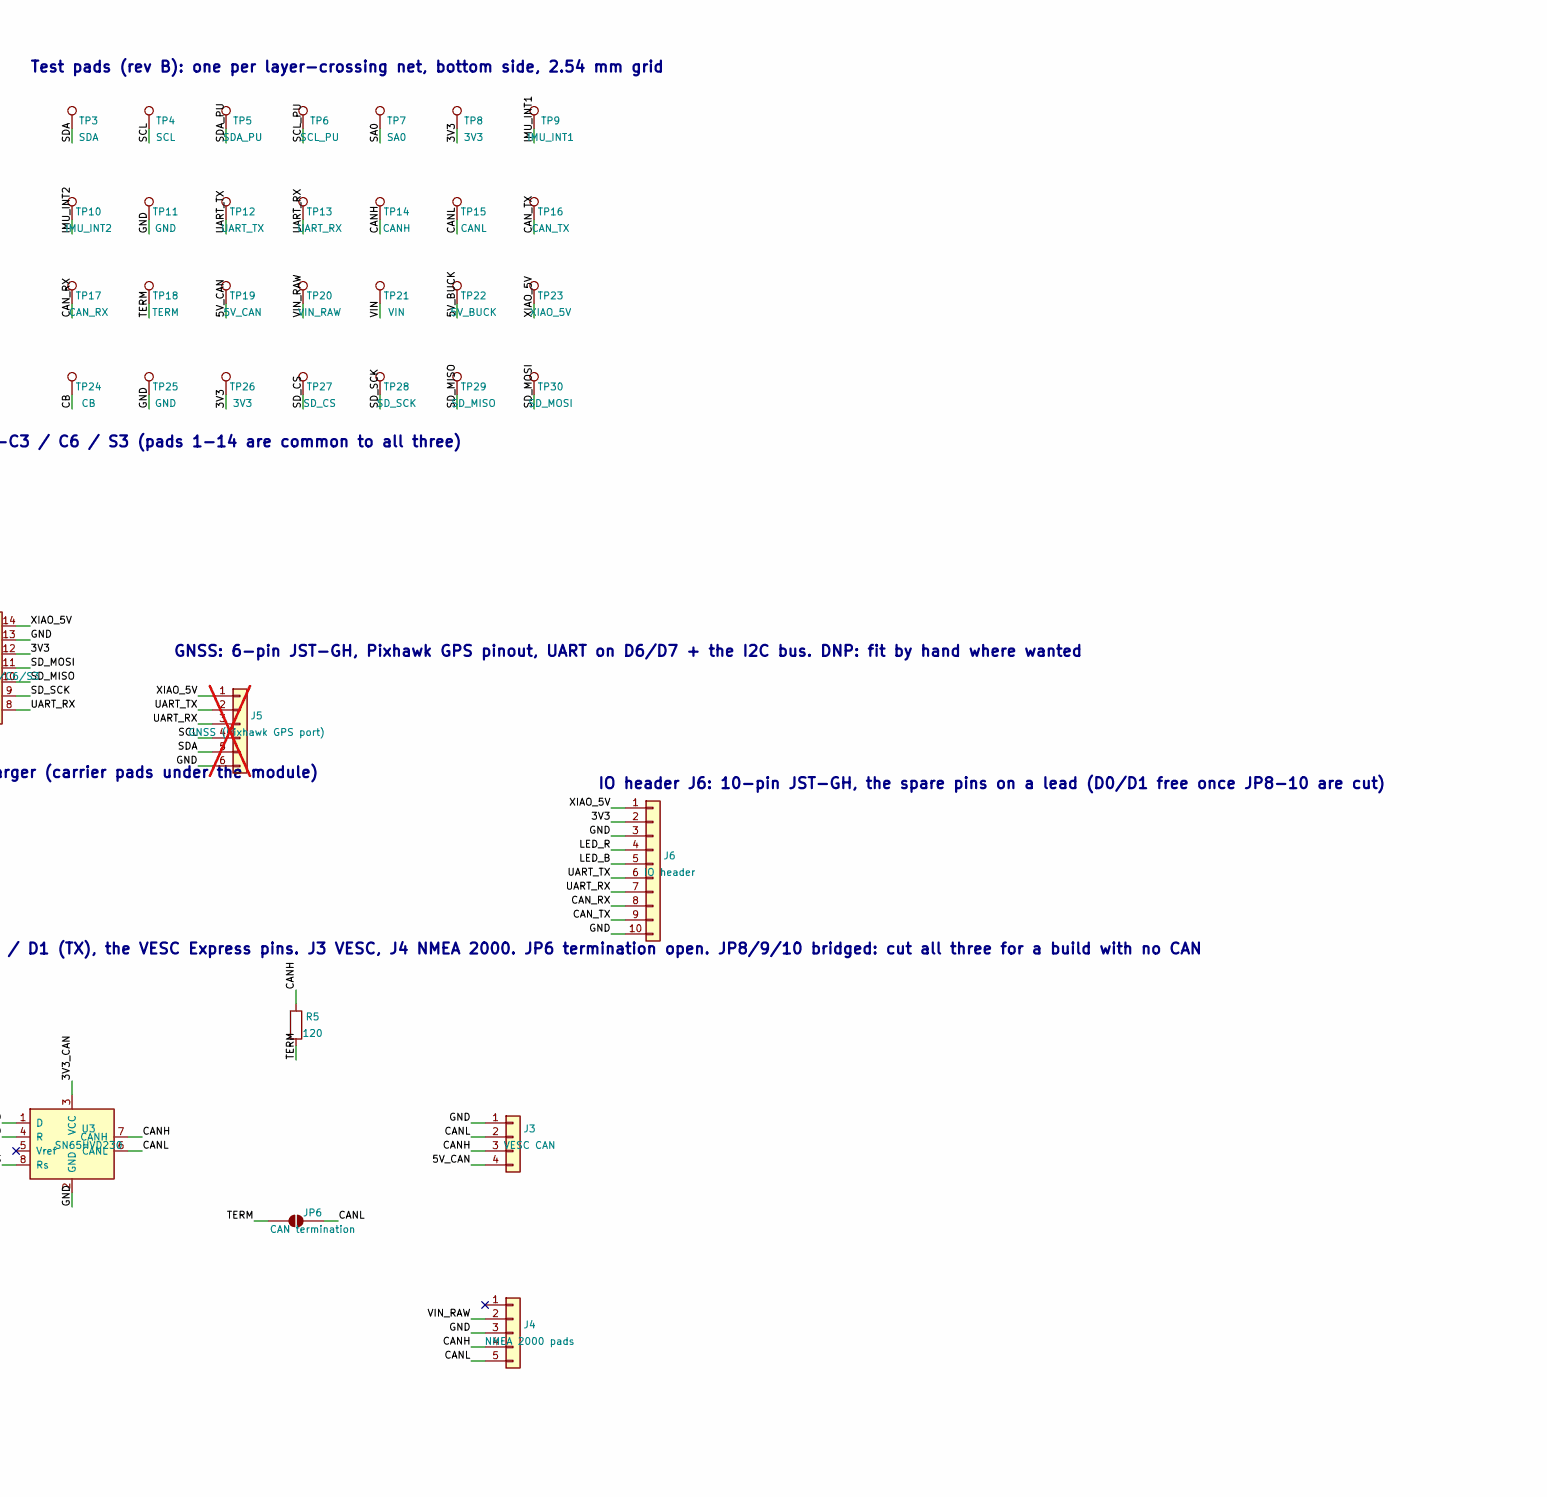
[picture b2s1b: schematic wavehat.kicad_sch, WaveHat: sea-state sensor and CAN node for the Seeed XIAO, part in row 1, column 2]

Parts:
C1, C3, C6, C7, C8: 100nF; C_0402_1005Metric; MPN GRM155R71C104KA88D
C2, C9: 10uF; C_0603_1608Metric; MPN GRM188R61A106KE69D
C4: 2.2uF 100V; C_1206_3216Metric; MPN GRM31CR72A225KA73L
C5: 22uF 10V; C_0805_2012Metric; MPN GRM21BR61A226ME51L
D1, D2, D3: SS14; D_SMA; MPN SS14
F1: 0.5A 60V; Fuse_1812_4532Metric; MPN 1812L050/60MR
FID1, FID2, FID3, FID4, FID5: Fiducial; Fiducial_1mm_Mask2mm
H1, H2: M2; MountingHole_2.2mm_M2_Pad
J2: Qwiic; JST_SH_SM04B-SRSS-TB_1x04-1MP_P1.00mm_Horizontal; MPN SM04B-SRSS-TB(LF)(SN)
J3: VESC CAN; JST_GH_SM04B-GHS-TB_1x04-1MP_P1.25mm_Horizontal; MPN SM04B-GHS-TB(LF)(SN)
J4: NMEA 2000 pads; N2K_Pads_1x05_P3.0mm
J5: GNSS (Pixhawk GPS port); JST_GH_SM06B-GHS-TB_1x06-1MP_P1.25mm_Horizontal; MPN SM06B-GHS-TB(LF)(SN); not fitted
J6: IO header; JST_GH_SM10B-GHS-TB_1x10-1MP_P1.25mm_Horizontal; MPN SM10B-GHS-TB(LF)(SN)
J7: BAT 1S LiPo (+ pin 1); PinHeader_1x02_P2.54mm_Vertical; not fitted
JP1: SDA pull-up; SolderJumper-2_P1.3mm_Bridged_RoundedPad1.0x1.5mm
JP2: SCL pull-up; SolderJumper-2_P1.3mm_Bridged_RoundedPad1.0x1.5mm
JP3: I2C addr 0x6B/0x6A; SolderJumper-3_P1.3mm_Bridged12_RoundedPad1.0x1.5mm
JP4: INT1 to D2; SolderJumper-2_P1.3mm_Open_RoundedPad1.0x1.5mm
JP5: INT2 to D3; SolderJumper-2_P1.3mm_Open_RoundedPad1.0x1.5mm
JP6: CAN termination; SolderJumper-2_P1.3mm_Open_RoundedPad1.0x1.5mm
JP7: SD CS on D3; SolderJumper-2_P1.3mm_Bridged_RoundedPad1.0x1.5mm
JP8: U3 3V3; SolderJumper-2_P1.3mm_Bridged_RoundedPad1.0x1.5mm
JP9: U3 RXD to D0; SolderJumper-2_P1.3mm_Bridged_RoundedPad1.0x1.5mm
JP10: U3 TXD to D1; SolderJumper-2_P1.3mm_Bridged_RoundedPad1.0x1.5mm
L1: 15uH; L_Changjiang_FNR4020S; MPN FNR4020S150MT
R1, R2: 4.7k; R_0402_1005Metric; MPN RC0402FR-074K7L
R3: 120k; R_0402_1005Metric; MPN RC0402FR-07120KL
R4: 22.1k; R_0402_1005Metric; MPN RC0402FR-0722K1L
R5: 120; R_0402_1005Metric; MPN RC0402FR-07120RL
R6, R9, R10, R11, R12: 10k; R_0402_1005Metric; MPN RC0402FR-0710KL
TP1: LED_R (D2); TestPoint_Pad_D1.5mm
TP2: LED_B (D3); TestPoint_Pad_D1.5mm
TP3: SDA; TestPoint_Pad_D1.0mm
TP4: SCL; TestPoint_Pad_D1.0mm
TP5: SDA_PU; TestPoint_Pad_D1.0mm
TP6: SCL_PU; TestPoint_Pad_D1.0mm
TP7: SA0; TestPoint_Pad_D1.0mm
TP8, TP26: 3V3; TestPoint_Pad_D1.0mm
TP9: IMU_INT1; TestPoint_Pad_D1.0mm
TP10: IMU_INT2; TestPoint_Pad_D1.0mm
TP11, TP25: GND; TestPoint_Pad_D1.0mm
TP12: UART_TX; TestPoint_Pad_D1.0mm
TP13: UART_RX; TestPoint_Pad_D1.0mm
TP14: CANH; TestPoint_Pad_D1.0mm
TP15: CANL; TestPoint_Pad_D1.0mm
TP16: CAN_TX; TestPoint_Pad_D1.0mm
TP17: CAN_RX; TestPoint_Pad_D1.0mm
TP18: TERM; TestPoint_Pad_D1.0mm
TP19: 5V_CAN; TestPoint_Pad_D1.0mm
TP20: VIN_RAW; TestPoint_Pad_D1.0mm
TP21: VIN; TestPoint_Pad_D1.0mm
TP22: 5V_BUCK; TestPoint_Pad_D1.0mm
TP23: XIAO_5V; TestPoint_Pad_D1.0mm
TP24: CB; TestPoint_Pad_D1.0mm
TP27: SD_CS; TestPoint_Pad_D1.0mm
TP28: SD_SCK; TestPoint_Pad_D1.0mm
TP29: SD_MISO; TestPoint_Pad_D1.0mm
TP30: SD_MOSI; TestPoint_Pad_D1.0mm
TVS1: SMBJ30A; D_SMB; MPN SMBJ30A
U1: LSM6DSO; LGA-14_3x2.5mm_P0.5mm_LayoutBorder3x4y; MPN LSM6DSOTR
U2: LMR51606Y; SOT-23-6; MPN LMR51606YDBVR
U3: SN65HVD230; SOIC-8_3.9x4.9mm_P1.27mm; MPN SN65HVD230DR
U4: XIAO ESP32-C3/C6/S3; XIAO_ESP32_14P_SMD; MPN Seeed XIAO ESP32C3 113991054 (or C6 113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
U5: SD NAND 2Gb (256 MB); SD_NAND_LGA-8_8x6mm_P1.27mm; MPN ZDSD02GLGEAG

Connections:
/3V3: C1.1, C2.1, C3.1, C8.1, C9.1, J2.2, J6.2, JP3.1 (A), JP8.1 (A), R1.1, R2.1, R9.1, R10.1, R11.1, R12.1, TP8.1, TP26.1, U1.5 (VDDIO), U1.8 (VDD), U1.12 (CS), U4.12 (3V3), U5.8 (VCC)
/3V3_CAN: C7.1, JP8.2 (B), U3.3 (VCC)
/5V_BUCK: C5.1, D2.2 (A), L1.2, R3.1, TP22.1
/5V_CAN: D3.2 (A), J3.4, TP19.1
/CANH: J3.3, J4.4, R5.1, TP14.1, U3.7 (CANH)
/CANL: J3.2, J4.5, JP6.2 (B), TP15.1, U3.6 (CANL)
/CAN_RX: J6.8, JP9.1 (A), TP17.1, U4.1 (D0)
/CAN_RXD: JP9.2 (B), U3.4 (R)
/CAN_TX: J6.9, JP10.1 (A), TP16.1, U4.2 (D1)
/CAN_TXD: JP10.2 (B), U3.1 (D)
/CB: C6.1, TP24.1, U2.1 (CB)
/FB: R3.2, R4.1, U2.3 (FB)
/GND: C1.2, C2.2, C3.2, C4.2, C5.2, C7.2, C8.2, C9.2, H1.1, H2.1, J2.1, J3.1, J4.3, J5.6, J6.3, J6.10, J7.2, JP3.3 (B), R4.2, R6.2, TP11.1, TP25.1, TVS1.2 (A), U1.2 (SDx), U1.3 (SCx), U1.6 (GND), U1.7 (GND), U2.2 (GND), U3.2 (GND), U4.13 (GND), U4.16 (GND(C3/S3)), U4.18 (GND(C6)), U5.4 (VSS)
/IMU_INT1: JP4.1 (A), TP9.1, U1.4 (INT1)
/IMU_INT2: JP5.1 (A), TP10.1, U1.9 (INT2)
/LED_B: J6.5, JP5.2 (B), JP7.1 (A), TP2.1, U4.4 (D3)
/LED_R: J6.4, JP4.2 (B), TP1.1, U4.3 (D2)
/RS: R6.1, U3.8 (Rs)
/SA0: JP3.2 (C), TP7.1, U1.1 (SDO/SA0)
/SCL: J2.4, J5.4, JP2.1 (A), TP4.1, U1.13 (SCL), U4.6 (D5/SCL)
/SCL_PU: JP2.2 (B), R2.2, TP6.1
/SDA: J2.3, J5.5, JP1.1 (A), TP3.1, U1.14 (SDA), U4.5 (D4/SDA)
/SDA_PU: JP1.2 (B), R1.2, TP5.1
/SD_CS: JP7.2 (B), R9.2, TP27.1, U5.2 (~CS)
/SD_MISO: R11.2, TP29.1, U4.10 (D9), U5.6 (DO)
/SD_MOSI: R12.2, TP30.1, U4.11 (D10), U5.5 (DI)
/SD_SCK: R10.2, TP28.1, U4.9 (D8), U5.3 (SCLK)
/SW: C6.2, L1.1, U2.6 (SW)
/TERM: JP6.1 (A), R5.2, TP18.1
/UART_RX: J5.3, J6.7, TP13.1, U4.8 (D7/RX)
/UART_TX: J5.2, J6.6, TP12.1, U4.7 (D6/TX)
/VBAT: J7.1, U4.15 (VBAT(C3/S3)), U4.17 (VBAT(C6))
/VIN: C4.1, D1.1 (K), TP21.1, TVS1.1 (K), U2.4 (EN), U2.5 (VIN)
/VIN_FUSED: D1.2 (A), F1.2
/VIN_RAW: F1.1, J4.2, TP20.1
/XIAO_5V: D2.1 (K), D3.1 (K), J5.1, J6.1, TP23.1, U4.14 (5V)

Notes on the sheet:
Power: NMEA 2000 NET-S or a 5-30 V lead on the J4 pads -> fuse -> reverse diode -> TVS -> LMR51606 buck 5 V -> diode-OR into the XIAO 5V pin
IMU: LSM6DSO on I2C, address 0x6B by default (JP3), as on the Takuma node
Controller: Seeed XIAO ESP32-C3 / C6 / S3 (pads 1-14 are common to all three)
GNSS: 6-pin JST-GH, Pixhawk GPS pinout, UART on D6/D7 + the I2C bus. DNP: fit by hand where wanted
Test pads (rev B): one per layer-crossing net, bottom side, 2.54 mm grid
CAN: SN65HVD230 on D0 (RX) / D1 (TX), the VESC Express pins. J3 VESC, J4 NMEA 2000. JP6 termination open. JP8/9/10 bridged: cut all three for a build with no CAN
IO header J6: 10-pin JST-GH, the spare pins on a lead (D0/D1 free once JP8-10 are cut)
BAT: 1S LiPo to the XIAO's own charger (carrier pads under the module)
Log storage: SD NAND on SPI, under the XIAO
Mechanical: M2 holes at the bow end

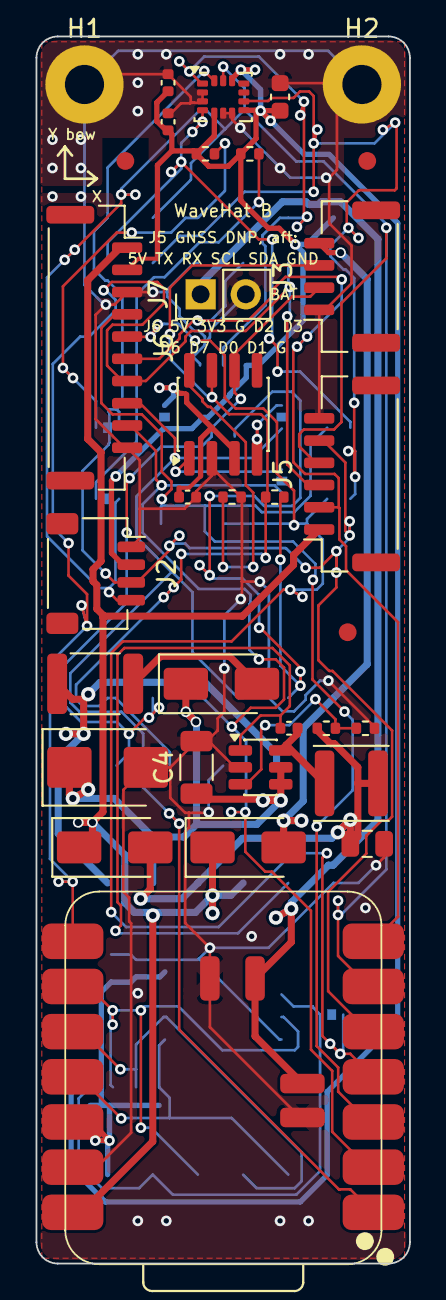
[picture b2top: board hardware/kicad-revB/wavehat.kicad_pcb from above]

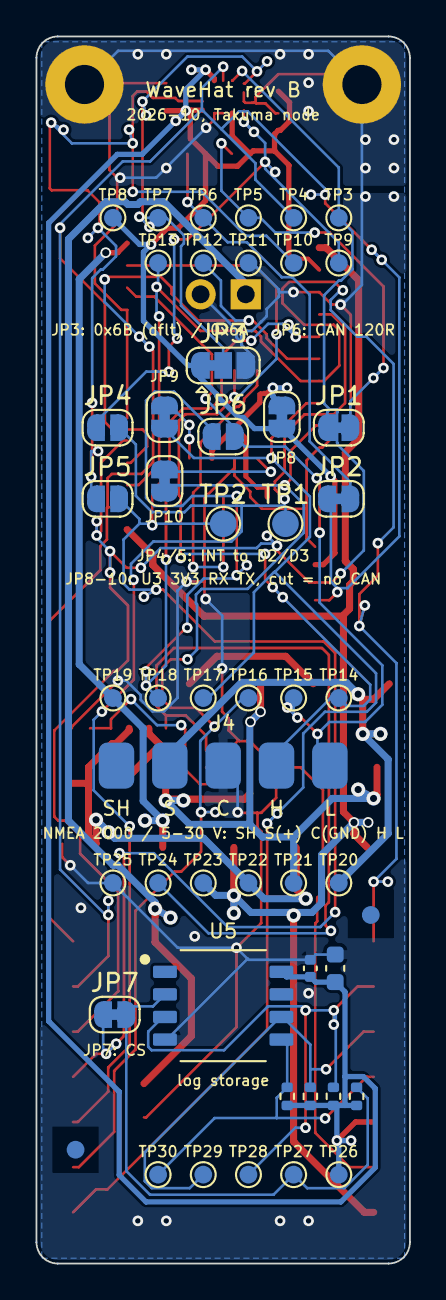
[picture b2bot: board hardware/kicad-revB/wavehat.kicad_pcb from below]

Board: 2 copper layers, 21.0 x 69.0 mm, 83 parts (50 on the bottom side), 36 nets.

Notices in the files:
hardware/kicad-revB/wavehat.kicad_sch:
XIAO footprint derived from Seeed OPL_Kicad_Library, CC BY-SA 4.0
parts and their libraries:
Derived from Seeed-Studio/OPL_Kicad_Library XIAO-ESP32-C3-SMD (CC BY-SA 4.0); the module-specific pads removed so one footprint fits all three variants, except the battery pads: 15/16 (C3 and S3 VBAT/GND) and 17/18 (C6, from Seeed C6 footprint).
